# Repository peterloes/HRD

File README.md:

# A Handheld Readout Device(HRD) for Battery Management Systems
Monitoring Battery Quality and reduce waste.

A standalone HRD to enable long-term diagnostic observations and 
documentation of battery quality.

Supported:

- TEXAS INSTRUMENTS bq40z50
- ATMEL ATmega32HVB

Rechargeable batteries are more and more dominating our modern life.
We find them in our smartphones and notebooks, in e-bikes and e-cars but also in many toys and
basically everywhere where wired power supply is absent.
The charge state of these batteries is usually reported by highlighting a certain portion of a bar, representing full charge.
But is this indication always correct and how can I check whether the full capacity of my battery is still available?

In many rechargeable batteries, technical parameters are controlled by a Battery Management System(BMS).
This device monitors physical parameters like Voltage, Current, Temperature and State of Charge but also
calculates useful values like "Total Number of Charge Cycles", "Total Operation Time since First Use "or"
Energy Delivered since Last Charge".

In product manufacturing, this information is important for checking the battery quality before final assembly
on the product. For battery-driven medical devices, reliable knowledge about the battery status can be crucial.
For the end-user of a battery driven device, access to these data would be beneficial to allow for an informed decision
whether the device could be repaired or needs to be replaced.
 
The efficient use of batteries is especially important, as batteries are difficult to recycle and thus constitute a
burden for the environment. Unfortunately, common BMSs do not display the stored data by default.

Battery controller probing requests. 0x0A=Atmel, 0x16=TI

Actual Current is signed.

Power management for the LC-Display.

Display will be scrolled (11 digits).

HRD can be connected to external devices like personal computers to transfer and store the extracted technical data.

https://github.com/peterloes/HRD/blob/master/Getting_Started_Tutorial/1_poster_overview.pdf

Manufacture:

https://github.com/peterloes/HRD/blob/master/Getting_Started_Tutorial/3_Supplier.txt

The standalone HRD features EFM32 ...the world´s most energy friendly microcontrollers

ARM Cortex-M3 EFM32G230F128

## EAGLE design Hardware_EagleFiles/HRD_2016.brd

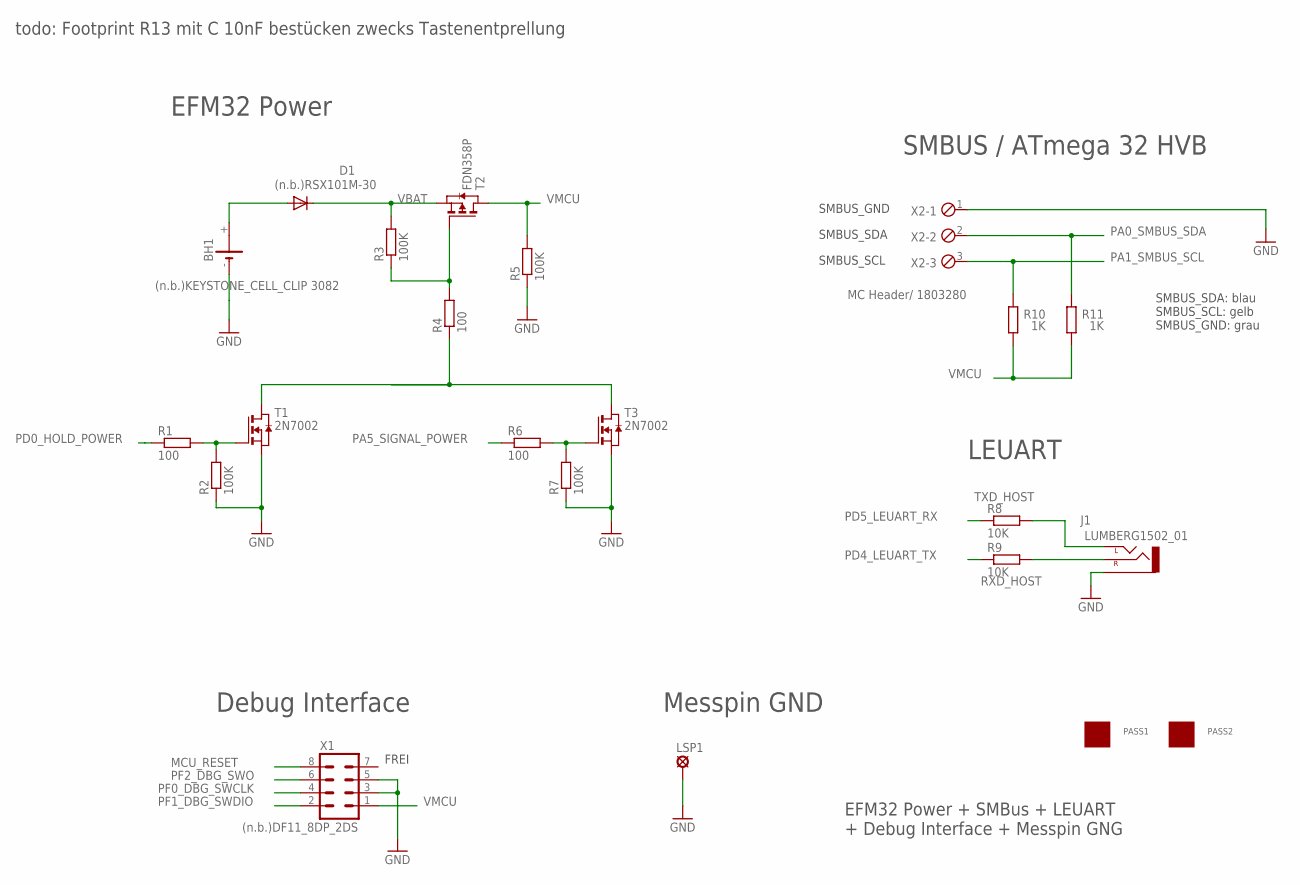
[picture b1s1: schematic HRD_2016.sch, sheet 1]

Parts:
BH1: (n.b.)KEYSTONE_CELL_CLIP 3082; 3082
D1: (n.b.)RSX101M-30; SOD123
J1: LUMBERG1502_01
LSP1: (n.b.)LSP13; LSP13
PASS1, PASS2: ROUND_1MM1.5; ROUND2_1.5MM
R1, R4, R6: 100; R0805
R2, R3, R5, R7: 100K; R0805
R8, R9: 10K; R0805
R10, R11: 1K; R0805
T1, T3: 2N7002; SOT-23
T2: FDN358P; ZETEX_SOT-23
X1: (n.b.)DF11_8DP_2DS; DP11_8DP-2DS
X2: MC Header/ 1803280; 3POL381

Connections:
GND: BH1.-, J1.P$1 (1-SLEEVE), LSP1.MP, R2.1, R5.1, R7.1, T1.2 (S), T3.2 (S), X1.3, X1.5, X2.1; also elsewhere on the board
MCU_RESET: X1.8; also elsewhere on the board
unnamed: BH1.+, D1.A
unnamed: R1.2, R2.2, T1.3 (G)
unnamed: R4.1, T1.1 (D), T3.1 (D)
unnamed: R6.2, R7.2, T3.3 (G)
unnamed: R3.1, R4.2, T2.3 (G)
PA0_SMBUS_SDA: R11.2, X2.2; also elsewhere on the board
PA1_SMBUS_SCL: R10.2, X2.3; also elsewhere on the board
PA5_SIGNAL_POWER: R6.1; also elsewhere on the board
PD0_HOLD_POWER: R1.1; also elsewhere on the board
PD4_LEUART_TX: R9.1; also elsewhere on the board
PD5_LEUART_RX: R8.1; also elsewhere on the board
PF0_DBG_SWCLK: X1.4; also elsewhere on the board
PF1_DBG_SWDIO: X1.2; also elsewhere on the board
PF2_DBG_SWO: X1.6; also elsewhere on the board
RXD_HOST: J1.P$3 (3-RIGHT), R9.2
TXD_HOST: J1.P$2 (2-LEFT), R8.2
VBAT: D1.C, R3.2, T2.2 (S); also elsewhere on the board
VMCU: R5.2, R10.1, R11.1, T2.1 (D), X1.1; also elsewhere on the board

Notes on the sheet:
EFM32 Power + SMBus + LEUART + Debug Interface + Messpin GNG
SMBUS_SCL
SMBUS_SDA
SMBUS_GND
EFM32 Power
Debug Interface
SMBUS / ATmega 32 HVB
FREI
SMBUS_SDA: blau SMBUS_SCL: gelb SMBUS_GND: grau
Messpin GND
LEUART
todo: Footprint R13 mit C 10nF bestücken zwecks Tastenentprellung

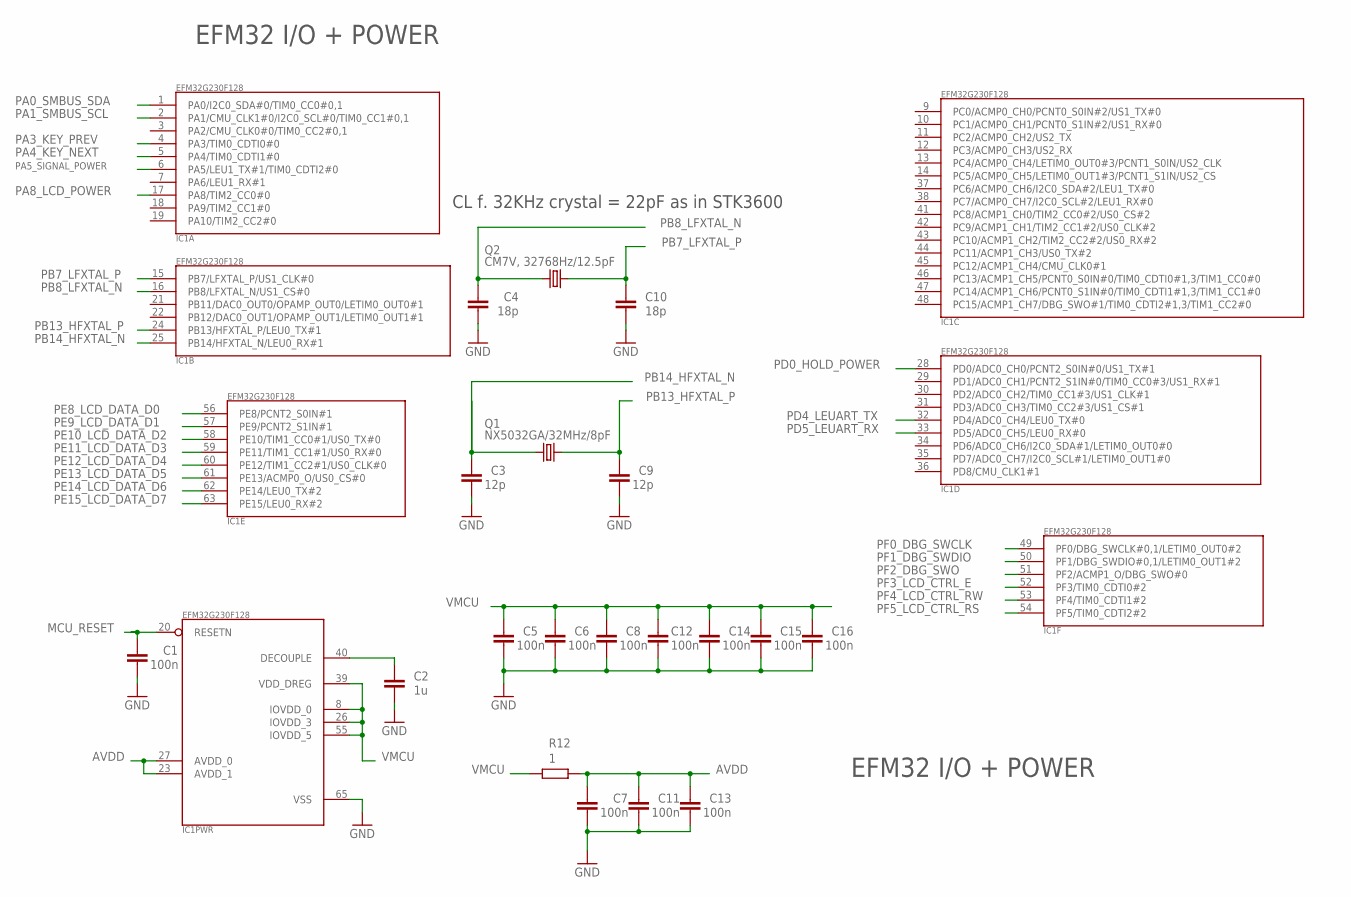
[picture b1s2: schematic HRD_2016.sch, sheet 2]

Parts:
C1, C5, C6, C7, C8, C11, C12, C13, C14, C15, C16: 100n; C0805K
C2: 1u; C0805K
C3, C9: 12p; C0805K
C4, C10: 18p; C0805K
IC1: EFM32G230F128; QFN64
Q1: NX5032GA/32MHz/8pF; CRYSTAL2P5.0X3.2
Q2: CM7V, 32768Hz/12.5pF; CRYSTAL2P3.2X1.5
R12: 1; R0805

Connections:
AVDD: C7.2, C11.2, C13.2, IC1.23 (AVDD_1), IC1.27 (AVDD_0), R12.2
GND: C1.1, C2.1, C3.1, C4.1, C5.1, C6.1, C7.1, C8.1, C9.1, C10.1, C11.1, C12.1, C13.1, C14.1, C15.1, C16.1, IC1.65 (VSS); also elsewhere on the board
MCU_RESET: C1.2, IC1.20 (RESETN); also elsewhere on the board
unnamed: C2.2, IC1.40 (DECOUPLE)
PA0_SMBUS_SDA: IC1.1 (PA0/I2C0_SDA#0/TIM0_CC0#0,1); also elsewhere on the board
PA1_SMBUS_SCL: IC1.2 (PA1/CMU_CLK1#0/I2C0_SCL#0/TIM0_CC1#0,1); also elsewhere on the board
PA3_KEY_PREV: IC1.4 (PA3/TIM0_CDTI0#0); also elsewhere on the board
PA4_KEY_NEXT: IC1.5 (PA4/TIM0_CDTI1#0); also elsewhere on the board
PA5_SIGNAL_POWER: IC1.6 (PA5/LEU1_TX#1/TIM0_CDTI2#0); also elsewhere on the board
PA8_LCD_POWER: IC1.17 (PA8/TIM2_CC0#0); also elsewhere on the board
PB7_LFXTAL_P: C10.2, IC1.15 (PB7/LFXTAL_P/US1_CLK#0), Q2.2
PB8_LFXTAL_N: C4.2, IC1.16 (PB8/LFXTAL_N/US1_CS#0), Q2.1
PB13_HFXTAL_P: C9.2, IC1.24 (PB13/HFXTAL_P/LEU0_TX#1), Q1.2
PB14_HFXTAL_N: C3.2, IC1.25 (PB14/HFXTAL_N/LEU0_RX#1), Q1.1
PD0_HOLD_POWER: IC1.28 (PD0/ADC0_CH0/PCNT2_S0IN#0/US1_TX#1); also elsewhere on the board
PD4_LEUART_TX: IC1.32 (PD4/ADC0_CH4/LEU0_TX#0); also elsewhere on the board
PD5_LEUART_RX: IC1.33 (PD5/ADC0_CH5/LEU0_RX#0); also elsewhere on the board
PE8_LCD_DATA_D0: IC1.56 (PE8/PCNT2_S0IN#1); also elsewhere on the board
PE9_LCD_DATA_D1: IC1.57 (PE9/PCNT2_S1IN#1); also elsewhere on the board
PE10_LCD_DATA_D2: IC1.58 (PE10/TIM1_CC0#1/US0_TX#0); also elsewhere on the board
PE11_LCD_DATA_D3: IC1.59 (PE11/TIM1_CC1#1/US0_RX#0); also elsewhere on the board
PE12_LCD_DATA_D4: IC1.60 (PE12/TIM1_CC2#1/US0_CLK#0); also elsewhere on the board
PE13_LCD_DATA_D5: IC1.61 (PE13/ACMP0_O/US0_CS#0); also elsewhere on the board
PE14_LCD_DATA_D6: IC1.62 (PE14/LEU0_TX#2); also elsewhere on the board
PE15_LCD_DATA_D7: IC1.63 (PE15/LEU0_RX#2); also elsewhere on the board
PF0_DBG_SWCLK: IC1.49 (PF0/DBG_SWCLK#0,1/LETIM0_OUT0#2); also elsewhere on the board
PF1_DBG_SWDIO: IC1.50 (PF1/DBG_SWDIO#0,1/LETIM0_OUT1#2); also elsewhere on the board
PF2_DBG_SWO: IC1.51 (PF2/ACMP1_O/DBG_SWO#0); also elsewhere on the board
PF3_LCD_CTRL_E: IC1.52 (PF3/TIM0_CDTI0#2); also elsewhere on the board
PF4_LCD_CTRL_RW: IC1.53 (PF4/TIM0_CDTI1#2); also elsewhere on the board
PF5_LCD_CTRL_RS: IC1.54 (PF5/TIM0_CDTI2#2); also elsewhere on the board
VMCU: C5.2, C6.2, C8.2, C12.2, C14.2, C15.2, C16.2, IC1.8 (IOVDD_0), IC1.26 (IOVDD_3), IC1.39 (VDD_DREG), IC1.55 (IOVDD_5), R12.1; also elsewhere on the board

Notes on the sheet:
EFM32 I/O + POWER
CL f. 32KHz crystal = 22pF as in STK3600

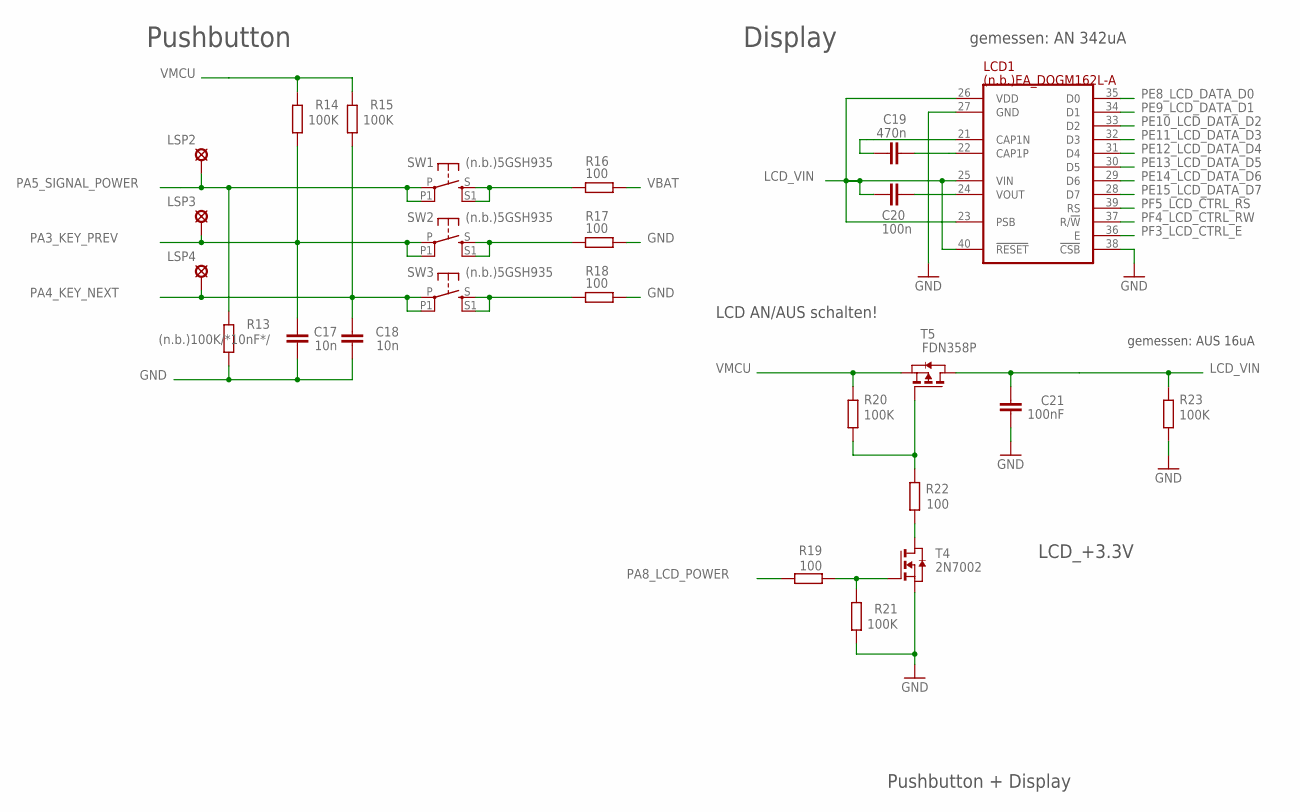
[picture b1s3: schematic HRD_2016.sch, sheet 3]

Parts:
C17, C18: 10n; C0603K
C19: 470n; C0603K
C20: 100n; C0603K
C21: 100nF; C0603K
LCD1: (n.b.)EA_DOGM162L-A; EA_DOGM
LSP2, LSP3, LSP4: (n.b.)SE13; SE13
R13: (n.b.)100K/*10nF*/; R0805
R14, R15, R20, R21, R23: 100K; R0805
R16, R17, R18, R19, R22: 100; R0805
SW1, SW2, SW3: (n.b.)5GSH935; MULTIMEC_5GSH935
T4: 2N7002; ZETEX_SOT-23
T5: FDN358P; ZETEX_SOT-23

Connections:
GND: C17.1, C18.1, C21.2, LCD1.27 (GND), LCD1.38 (!CSB!), R13.1, R17.2, R18.2, R21.1, R23.1, T4.2 (S); also elsewhere on the board
LCD_VIN: C20.2, C21.1, LCD1.23 (PSB), LCD1.25 (VIN), LCD1.26 (VDD), LCD1.40 (!RESET!), R23.2, T5.1 (D)
unnamed: R17.1, SW2.S, SW2.S1
unnamed: R16.1, SW1.S, SW1.S1
unnamed: R18.1, SW3.S, SW3.S1
unnamed: R20.1, R22.2, T5.3 (G)
unnamed: R22.1, T4.1 (D)
unnamed: R19.1, R21.2, T4.3 (G)
unnamed: C19.2, LCD1.22 (CAP1P)
unnamed: C19.1, LCD1.21 (CAP1N)
unnamed: C20.1, LCD1.24 (VOUT)
PA3_KEY_PREV: C17.2, LSP3.MP, R14.1, SW2.P, SW2.P1; also elsewhere on the board
PA4_KEY_NEXT: C18.2, LSP4.MP, R15.1, SW3.P, SW3.P1; also elsewhere on the board
PA5_SIGNAL_POWER: LSP2.MP, R13.2, SW1.P, SW1.P1; also elsewhere on the board
PA8_LCD_POWER: R19.2; also elsewhere on the board
PE8_LCD_DATA_D0: LCD1.35 (D0); also elsewhere on the board
PE9_LCD_DATA_D1: LCD1.34 (D1); also elsewhere on the board
PE10_LCD_DATA_D2: LCD1.33 (D2); also elsewhere on the board
PE11_LCD_DATA_D3: LCD1.32 (D3); also elsewhere on the board
PE12_LCD_DATA_D4: LCD1.31 (D4); also elsewhere on the board
PE13_LCD_DATA_D5: LCD1.30 (D5); also elsewhere on the board
PE14_LCD_DATA_D6: LCD1.29 (D6); also elsewhere on the board
PE15_LCD_DATA_D7: LCD1.28 (D7); also elsewhere on the board
PF3_LCD_CTRL_E: LCD1.36 (E); also elsewhere on the board
PF4_LCD_CTRL_RW: LCD1.37 (R/!W!); also elsewhere on the board
PF5_LCD_CTRL_RS: LCD1.39 (RS); also elsewhere on the board
VBAT: R16.2; also elsewhere on the board
VMCU: R14.2, R15.2, R20.2, T5.2 (S); also elsewhere on the board

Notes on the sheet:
Pushbutton + Display
Display
gemessen: AUS 16uA
LCD_+3.3V
LCD AN/AUS schalten!
gemessen: AN 342uA
Pushbutton

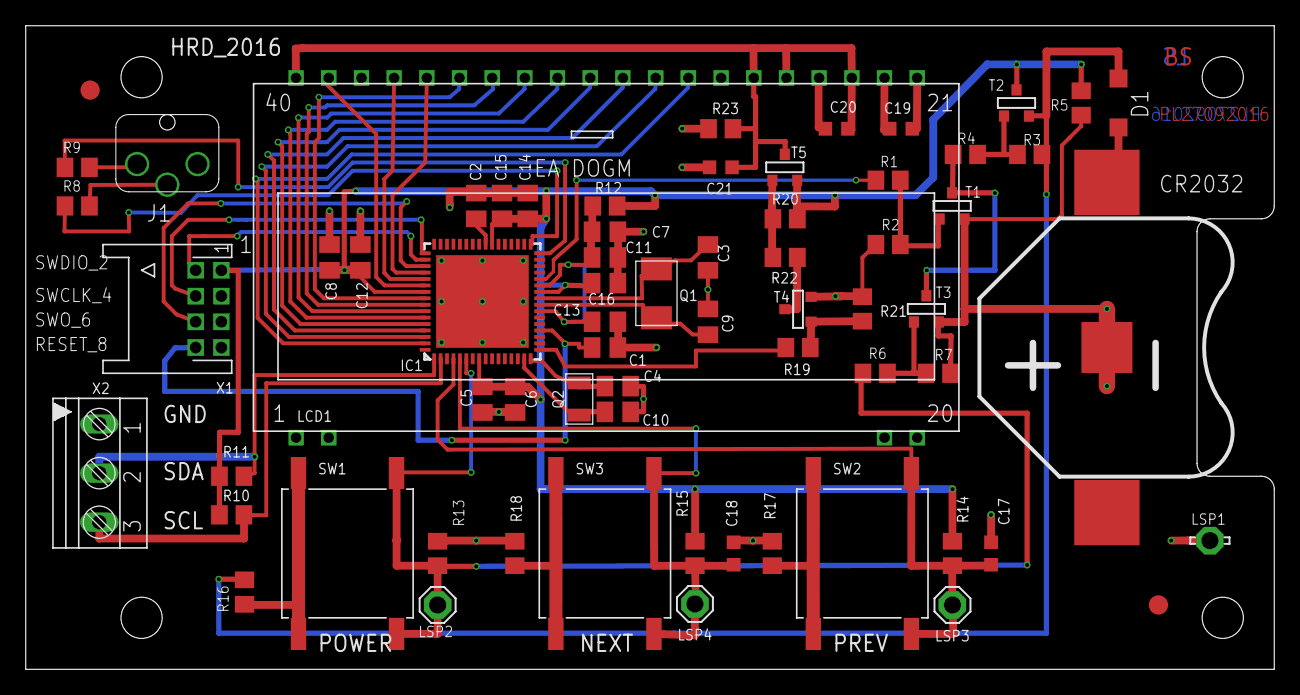
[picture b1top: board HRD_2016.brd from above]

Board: 2 copper layers, 97.0 x 50.0 mm, 67 parts (0 on the bottom side), 50 nets.

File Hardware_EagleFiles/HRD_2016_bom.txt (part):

Part  Value                         Device           Package          Description                                                    MF MPN OC_FARNELL OC_NEWARK
BH1   (n.b.)KEYSTONE_CELL_CLIP 3082 3082             3082                                                                                                       
C1    100n                          C-EUC0805K       C0805K           CAPACITOR, European symbol                                                                
C2    1u                            C-EUC0805K       C0805K           CAPACITOR, European symbol                                                                
C3    12p                           C-EUC0805K       C0805K           CAPACITOR, European symbol                                                                
C4    18p                           C-EUC0805K       C0805K           CAPACITOR, European symbol                                                                
C5    100n                          C-EUC0805K       C0805K           CAPACITOR, European symbol                                                                
C6    100n                          C-EUC0805K       C0805K           CAPACITOR, European symbol                                                                
C7    100n                          C-EUC0805K       C0805K           CAPACITOR, European symbol                                                                
C8    100n                          C-EUC0805K       C0805K           CAPACITOR, European symbol                                                                
C9    12p                           C-EUC0805K       C0805K           CAPACITOR, European symbol                                                                
C10   18p                           C-EUC0805K       C0805K           CAPACITOR, European symbol                                                                
C11   100n                          C-EUC0805K       C0805K           CAPACITOR, European symbol                                                                
C12   100n                          C-EUC0805K       C0805K           CAPACITOR, European symbol                                                                
C13   100n                          C-EUC0805K       C0805K           CAPACITOR, European symbol                                                                
C14   100n                          C-EUC0805K       C0805K           CAPACITOR, European symbol                                                                
C15   100n                          C-EUC0805K       C0805K           CAPACITOR, European symbol                                                                
C16   100n                          C-EUC0805K       C0805K           CAPACITOR, European symbol                                                                
C17   10n                           C-EUC0603K       C0603K           CAPACITOR, European symbol                                                                
C18   10n                           C-EUC0603K       C0603K           CAPACITOR, European symbol                                                                
C19   470n                          C-EUC0603K       C0603K           CAPACITOR, European symbol                                                                
C20   100n                          C-EUC0603K       C0603K           CAPACITOR, European symbol                                                                
C21   100nF                         C-EUC0603K       C0603K           CAPACITOR, European symbol                                                                
D1    (n.b.)RSX101M-30              DIODE-SOD123     SOD123           DIODE                                                                                     
IC1   EFM32G230F128                 EFM32G230F128    QFN64            EFM32G230F128 Gecko Microcontroller in 9mm x 9mm QFN64 package                            
J1    LUMBERG1502_01                LUMBERG1502_01   LUMBERG1502_01                                                                                             
LCD1  (n.b.)EA_DOGM162L-A           EA_DOGM162       EA_DOGM          ELECTRONIC ASSEMBYL GmbH                                                                  
LSP1  (n.b.)LSP13                   LSP13            LSP13            SOLDER PAD drill 1.3 mm, distributor Buerklin, 12H562                                     
LSP2  (n.b.)SE13                    SE13             SE13             SOLDER PAD E1542,  drill 1,3mm, distributor Buerklin, 07F815                              
LSP3  (n.b.)SE13                    SE13             SE13             SOLDER PAD E1542,  drill 1,3mm, distributor Buerklin, 07F815                              
LSP4  (n.b.)SE13                    SE13             SE13             SOLDER PAD E1542,  drill 1,3mm, distributor Buerklin, 07F815                              
PASS1 ROUND_1MM1.5                  ROUND_1MM1.5     ROUND2_1.5MM                                                                                               
PASS2 ROUND_1MM1.5                  ROUND_1MM1.5     ROUND2_1.5MM                                                                                               
Q1    NX5032GA/32MHz/8pF            CRYSTAL2P5.0X3.2 CRYSTAL2P5.0X3.2 Quarz Crystal                                                                             
Q2    CM7V, 32768Hz/12.5pF          CRYSTAL2P        CRYSTAL2P3.2X1.5 Quarz Crystal                                                                             
R1    100                           R-EU_R0805       R0805            RESISTOR, European symbol                                                                 
R2    100K                          R-EU_R0805       R0805            RESISTOR, European symbol                                                                 
R3    100K                          R-EU_R0805       R0805            RESISTOR, European symbol                                                                 
R4    100                           R-EU_R0805       R0805            RESISTOR, European symbol                                                                 
R5    100K                          R-EU_R0805       R0805            RESISTOR, European symbol                                                                 
R6    100                           R-EU_R0805       R0805            RESISTOR, European symbol                                                                 
R7    100K                          R-EU_R0805       R0805            RESISTOR, European symbol                                                                 
R8    10K                           R-EU_R0805       R0805            RESISTOR, European symbol                                                                 
R9    10K                           R-EU_R0805       R0805            RESISTOR, European symbol                                                                 
R10   1K                            R-EU_R0805       R0805            RESISTOR, European symbol                                                                 
R11   1K                            R-EU_R0805       R0805            RESISTOR, European symbol                                                                 
R12   1                             R-EU_R0805       R0805            RESISTOR, European symbol                                                                 
R13   (n.b.)100K                    R-EU_R0805       R0805            RESISTOR, European symbol                                                                 
R14   100K                          R-EU_R0805       R0805            RESISTOR, European symbol                                                                 
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

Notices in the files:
parts and their libraries:
EnergyMicro: CC0 License
SparkFun-Aesthetics: Licensing: CC v3.0 Share-Alike You are welcome to use this library for commercial purposes.
